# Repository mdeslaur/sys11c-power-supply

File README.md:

# Williams System 11B/11C Power Supply

This is a replacement power supply for use in Williams System 11B/11C
pinball machines. The original part number is D-12246.

When being used with low-voltage LED displays, all parts in the 100v
sections can be left unpopulated.

It is in KiCad 7 format.

See Docs/parts-list.txt for a list of parts. Make sure the regulator is
installed the right way. The square pad is pin 1, and the pin numbers are
printed on it. Also, you can use either the bridge rectifier, or individual
diodes, don't install both.

The gerbers for JLCPCB are in the zip file in the gerbers directory.

This has been tested in both a Williams Taxi and a Williams Diner with
low-voltage LED displays. The high-voltage section has not been tested, so
please let me know if it works.

Change history:  
1.0 - Initial version  

To Do:  
- Change silkscreen for regulator to better indicate orientation  
- Make sure there's enough room for the Q1 and Q3 heatsinks

Marc Deslauriers  
2024-01-31

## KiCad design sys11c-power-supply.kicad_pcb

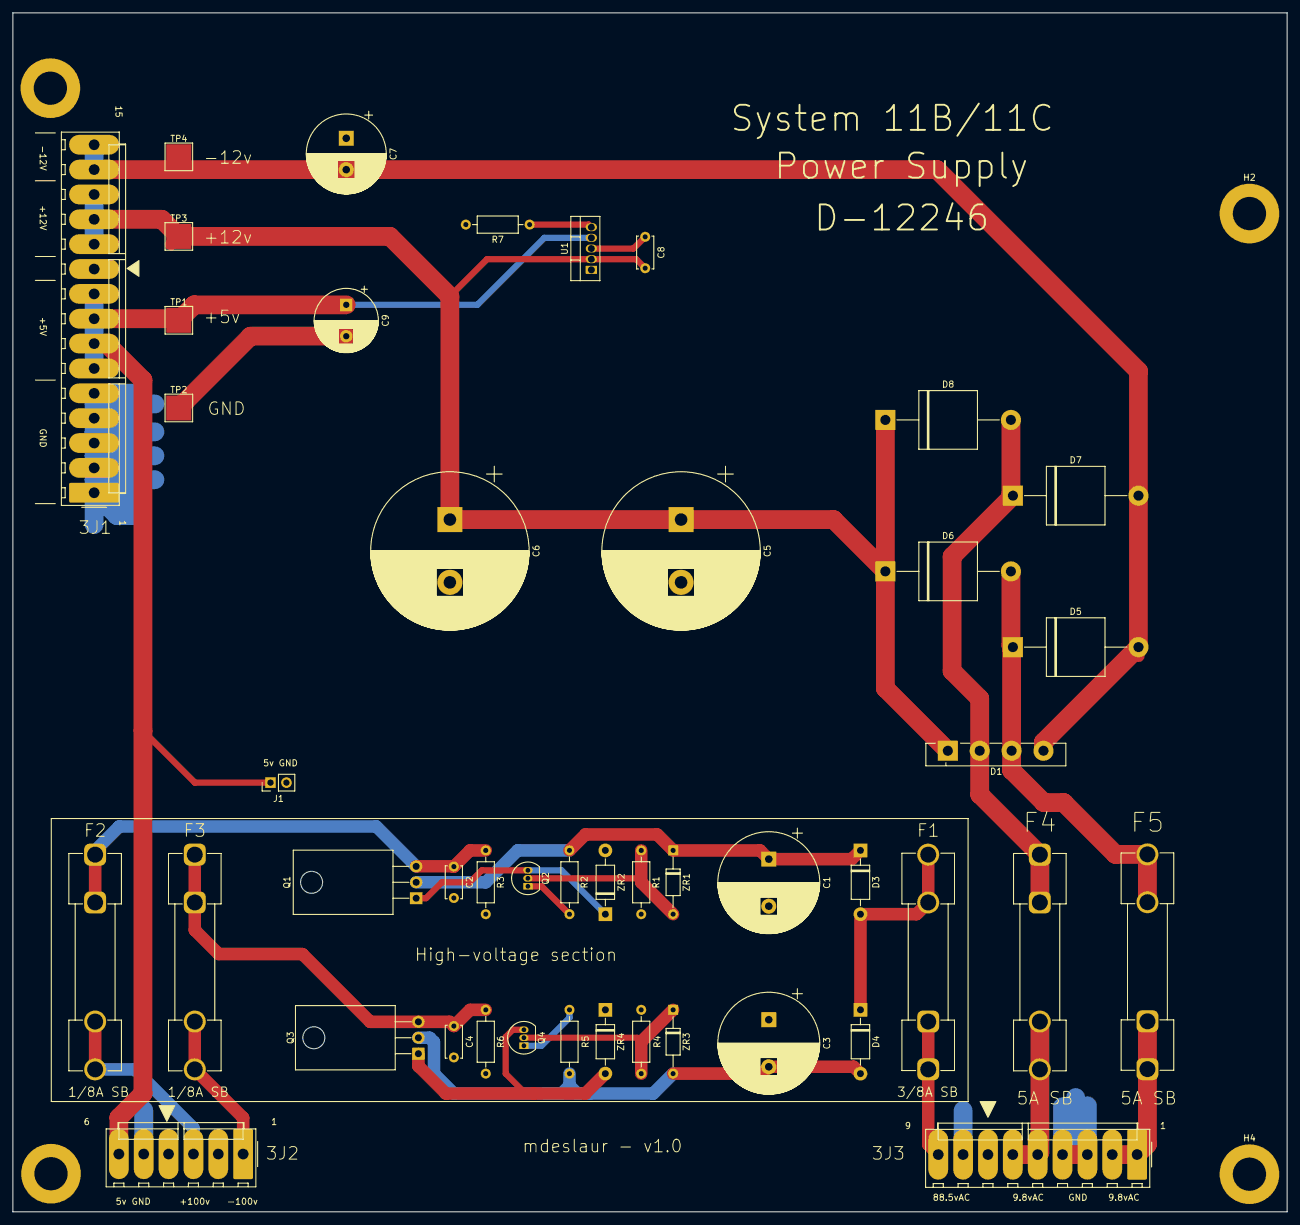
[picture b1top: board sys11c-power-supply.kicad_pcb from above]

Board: 2 copper layers, 203.0 x 191.0 mm, 49 parts (0 on the bottom side), 23 nets.

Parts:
3J1: Conn_01x15; Molex_KK-396_A-41791-0015_1x15_P3.96mm_Vertical
3J2: Conn_01x06; Molex_KK-396_A-41791-0006_1x06_P3.96mm_Vertical
3J3: Conn_01x09; Molex_KK-396_A-41791-0009_1x09_P3.96mm_Vertical
C1, C3: 150uF 160v; CP_Radial_D16.0mm_P7.50mm
C2, C4: 0.1uF; C_Disc_D5.0mm_W2.5mm_P5.00mm
C5, C6: 10,000uF; CP_Radial_D25.0mm_P10.00mm_SnapIn
C7: 1000uF; CP_Radial_D12.5mm_P5.00mm
C8: 22uF Cer; C_Disc_D5.0mm_W2.5mm_P5.00mm
C9: 2200uF 16V; CP_Radial_D10.0mm_P5.00mm
D1: GBU6B; Diode_Bridge_Vishay_GBU
D3, D4: 1N4004; D_DO-41_SOD81_P10.16mm_Horizontal
D5, D6, D7, D8: D_Filled; D_P600_R-6_P20.00mm_Horizontal
F1: 3/8A SB; Fuseholder_Clip-6.3x32mm_Littelfuse_102_Inline_P34.21x7.62m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
F2, F3: 1/8A SB; Fuseholder_Clip-6.3x32mm_Littelfuse_102_Inline_P34.21x7.62m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
F4, F5: 5A SB; Fuseholder_Clip-6.3x32mm_Littelfuse_102_Inline_P34.21x7.62m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
H1, H2, H3, H4: MountingHole_Pad; MountingHole_5.3mm_M5_ISO7380_Pad
J1: Optional Voltmeter; PinHeader_1x02_P2.54mm_Vertical
Q1: MJE15030; TO-220-3_Horizontal_TabDown
Q2: 2N5401; TO-92_Inline
Q3: MJE15031; TO-220-3_Horizontal_TabDown
Q4: 2N5551; TO-92_Inline
R1, R4: 39K 1W; R_Axial_DIN0207_L6.3mm_D2.5mm_P10.16mm_Horizontal
R2, R5: 680 1/2W; R_Axial_DIN0207_L6.3mm_D2.5mm_P10.16mm_Horizontal
R3, R6: 330K 1/2W; R_Axial_DIN0207_L6.3mm_D2.5mm_P10.16mm_Horizontal
R7: 267 1%; R_Axial_DIN0207_L6.3mm_D2.5mm_P10.16mm_Horizontal
TP1: +5v TP; TestPoint_Pad_4.0x4.0mm
TP2: GND TP; TestPoint_Pad_4.0x4.0mm
TP3: +12v TP; TestPoint_Pad_4.0x4.0mm
TP4: -12v TP; TestPoint_Pad_4.0x4.0mm
U1: PTR08060WVD; TO-220-5_Vertical
ZR1, ZR3: 1N5990; D_DO-35_SOD27_P10.16mm_Horizontal
ZR2, ZR4: 1N4764; D_DO-41_SOD81_P10.16mm_Horizontal

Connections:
/+5v: 3J1.6, 3J1.7, 3J1.8, 3J1.9, 3J2.6, C9.1, J1.1, TP1.1, U1.4 (VO)
/+12v Unreg: 3J1.11, 3J1.12, 3J1.13, C5.1, C6.1, C8.1, D1.1 (+), D6.1 (K), D8.1 (K), TP3.1, U1.2 (VI)
/+100v: 3J2.3, F2.2
/-12v Unreg: 3J1.14, 3J1.15, C7.2, D1.4 (-), D5.2 (A), D7.2 (A), TP4.1
/-100v: 3J2.1, F3.2
GND: 3J1.1, 3J1.2, 3J1.3, 3J1.4, 3J1.5, 3J2.5, 3J3.3, 3J3.4, 3J3.8, C1.2, C2.2, C3.1, C4.2, C5.2, C6.2, C7.1, C8.2, C9.2, H1.1, H2.1, H3.1, H4.1, J1.2, R1.2, R3.2, R4.2, R6.2, R7.2, TP2.1, U1.3 (GND), ZR2.2 (A), ZR4.1 (K)
unnamed: 3J3.1, 3J3.2, F5.1
unnamed: 3J3.5, 3J3.6, F4.2
unnamed: 3J3.9, F1.1
unnamed: D3.2 (A), D4.1 (K), F1.2
unnamed: C1.1, D3.1 (K), Q1.2 (C), R2.1, ZR1.1 (K)
unnamed: C3.2, D4.2 (A), Q3.2 (C), R5.1, ZR3.2 (A)
unnamed: D1.3, D5.1 (K), D6.2 (A), F5.2
unnamed: D1.2, D7.1 (K), D8.2 (A), F4.1
unnamed: Q1.1 (B), Q2.3 (C), ZR2.1 (K)
unnamed: C2.1, F2.1, Q1.3 (E), R3.1
unnamed: Q2.2 (B), R1.1, ZR1.2 (A)
unnamed: Q2.1 (E), R2.2
unnamed: Q3.1 (B), Q4.3 (C), ZR4.2 (A)
unnamed: C4.1, F3.1, Q3.3 (E), R6.1
unnamed: Q4.2 (B), R4.1, ZR3.1 (K)
unnamed: Q4.1 (E), R5.2
unnamed: R7.1, U1.5 (VOADJUST)

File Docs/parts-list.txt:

Parts List:

Main section:

U1 - PTR08060WVD Texas Instruments Switching Regulator
D1 - 6A Bridge GBU6B
D5-D8 - 6A diodes GI751 (optional, instead of D1)
C5,C6 - 10,000uF 20v Electrolytic Capacitor
C7 - 1000uF 25v Electrolytic Capacitor
C8 - 22uF 20v Ceramic Capacitor
C9 - 2200uF 16v Electrolytic Capacitor
R7 - 267 ohm, 1/4W, 1% resistor
F4,F5 - Fuse clips, 5A SB fuse
3J1 - Molex 3.96MM 15-pin header
3J2 - Molex 3.96MM 6-pin header
3J3 - Molex 3.96MM 9-pin header

Optional high-voltage section:
(Not used when low-voltage LED displays are used)

Q1 - MJE15030 transistor
Q2 - 2N5401 transistor
Q3 - MJE15031 transistor
Q4 - 2N5551 transistor
C1,C3 - 150uF 160v Electrolytic Capacitor
C2,C4 - 0.1uF 500v Ceramic capacitor
R1,R4 - 39K ohm 1W resistor
R2,R5 - 680 ohm 1/2W resistor
R3,R6 - 300K ohm 1/2W resistor
ZR1,ZR3 - 1N5990 Zener diode
ZR2,ZR4 - 1N4764 Zener diode
F1 - Fuse clips, 3/8A SB fuse
F2,F3 - Fuse clips, 1/8A SB fuse

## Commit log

2024-02-14 clarify use of bridge or diodes
2024-02-14 fix typo
2024-02-14 add heatsinks to parts list and add a todo to check space for them
2024-05-30 README.md: mention being tested in Diner
